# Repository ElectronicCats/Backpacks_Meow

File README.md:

# Backpacks Meow Meow

> WARNING: The Backpacks for Meow Meow are very much still under development and subject to change. If you would like to contribute features and ideas, please send pullrequest to this github repository or file an issue.

## Backpacks

### JACDAC

The JACDAC Connect system uses the JACDAC (Joint Asynchronous Communications) protocol, a single cable transmission protocol for the plug and play of accessories for microcontrollers.

We have adapted this technology to unlock the following benefits:

- No welding between JACDAC breakouts
- Connectors with 3.5mm audio plug to avoid connection errors.
- Ability to create a chain in series where you can connect multiple devices.

More [info about JACDAC](https://jacdac.org/)

### BLE HID
Add wireless connection functionality to your Meow Meow thanks to bluetooth 4.0

## LICENSE

Hardware released under an CERN Open Hardware Licence v1.2. See the LICENSE_HARDWARE file for more information.

Designed by Electronic Cats.

Electronic Cats is a registered trademark, please do not use if you sell these PCBs.

Electronic Cats invests time and resources providing this open source design, please support Electronic Cats and open-source hardware by purchasing products from Electronic Cats!

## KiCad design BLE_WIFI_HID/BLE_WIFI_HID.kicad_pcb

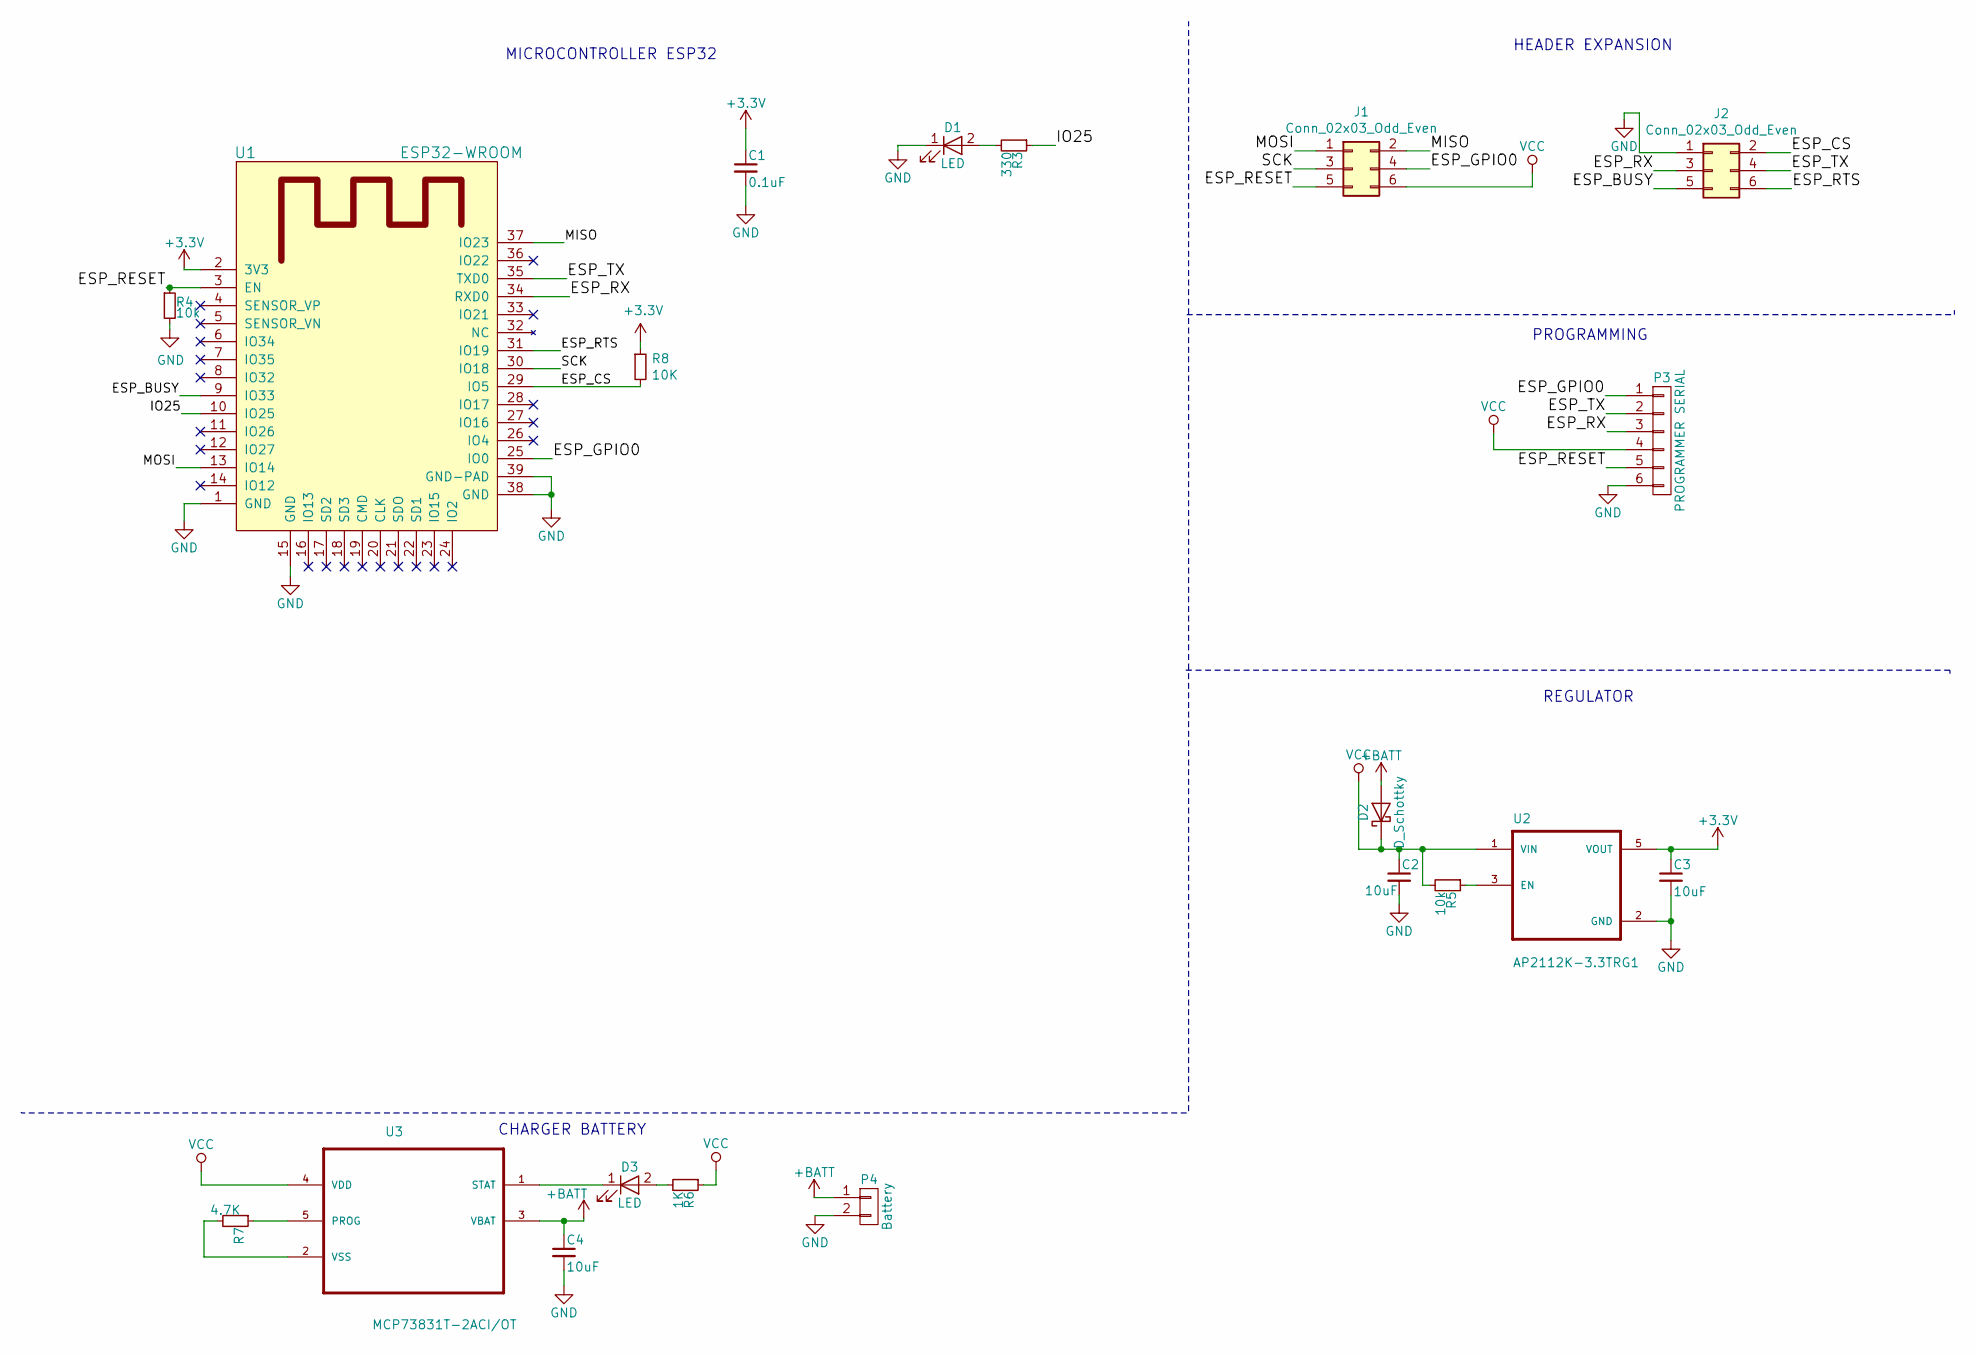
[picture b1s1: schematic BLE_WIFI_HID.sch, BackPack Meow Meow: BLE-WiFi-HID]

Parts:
C1: 0.1uF; C_0805_HandSoldering
C2, C3, C4: 10uF; C_0805_HandSoldering
D1, D3: LED; LED_0805_HandSoldering
D2: D_Schottky; D_SOD-123F
J1, J2: Conn_02x03_Odd_Even; 62000621121
P3: PROGRAMMER SERIAL; Pin_Header_Straight_1x06_Pitch2.54mm
P4: Battery; Pin_Header_Straight_1x02_Pitch2.54mm
R3: 330; R_0805_HandSoldering
R4, R5: 10k; R_0805_HandSoldering
R6: 1K; R_0805_HandSoldering
R7: 4.7K; R_0805_HandSoldering
R8: 10K; R_0805_HandSoldering
U1: ESP32-WROOM
U2: AP2112K-3.3TRG1; SOT-23-5_HandSoldering
U3: MCP73831T-2ACI/OT; SOT-23-5_HandSoldering

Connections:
+3V3: C1.1, C3.1, R8.1, U1.2 (3V3), U2.5 (VOUT)
+BATT: C4.1, D2.2 (A), P4.1, U3.3 (VBAT); also elsewhere on the board
/ESP_BUSY: J2.5, U1.9 (IO33)
/ESP_CS: J2.2, R8.2, U1.29 (IO5)
/ESP_GPIO0: J1.4, P3.1, U1.25 (IO0)
/ESP_RESET: J1.5, P3.5, R4.1, U1.3 (EN)
/ESP_RTS: J2.6, U1.31 (IO19)
/ESP_RX: J2.3, P3.3, U1.34 (RXD0)
/ESP_TX: J2.4, P3.2, U1.35 (TXD0)
/IO25: R3.1, U1.10 (IO25)
/MISO: J1.2, U1.37 (IO23)
/MOSI: J1.1, U1.13 (IO14)
/SCK: J1.3, U1.30 (IO18)
GND: C1.2, C2.2, C3.2, C4.2, D1.1 (K), J2.1, P3.6, P4.2, R4.2, U1.1 (GND), U1.15 (GND), U1.38 (GND), U1.39 (GND-PAD), U2.2 (GND); also elsewhere on the board
unnamed: D1.2 (A), R3.2
unnamed: D3.1 (K), U3.1 (STAT)
unnamed: D3.2 (A), R6.2
unnamed: R5.1, U2.3 (EN)
unnamed: R7.1, U3.5 (PROG)
unnamed: R7.2, U3.2 (VSS)
VCC: C2.1, D2.1 (K), J1.6, P3.4, R5.2, R6.1, U2.1 (VIN), U3.4 (VDD)

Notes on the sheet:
MICROCONTROLLER ESP32
HEADER EXPANSION
PROGRAMMING
CHARGER BATTERY
REGULATOR

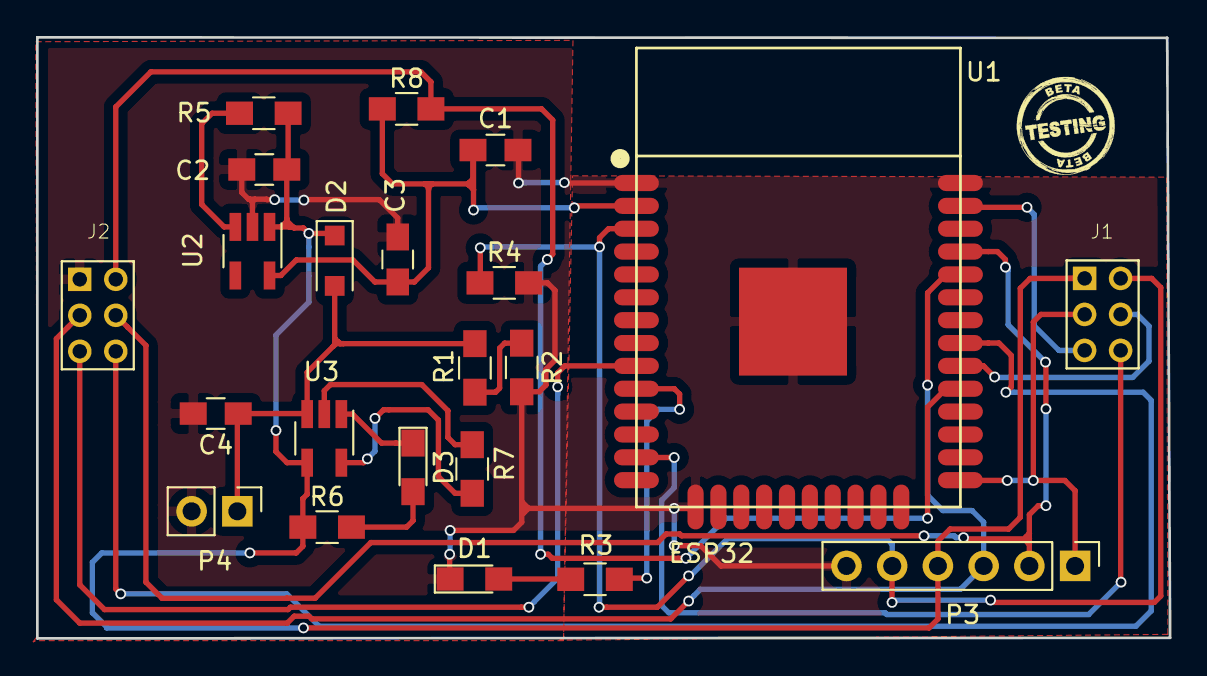
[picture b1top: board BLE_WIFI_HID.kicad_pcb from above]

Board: 2 copper layers, 62.9 x 33.4 mm, 22 parts (0 on the bottom side), 22 nets.

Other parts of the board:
R1, R2: 100k; R_0805_HandSoldering

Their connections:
+BATT: R1.1; also elsewhere on the board
/AN35_BAT: R1.2, R2.1
GND: R2.2; also elsewhere on the board

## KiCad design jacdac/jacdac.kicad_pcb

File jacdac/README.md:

# Make JACDAC System with Meow Meow Backpack

> **Status Tutorial: Experimental**

This tutorial shows you how to build your own MakeCode JACDAC using an [Meow Meow](https://www.electroniccats.com) as the controller sensors device.

## Parts needed

Before you begin, you're going to need a few parts which are shown in the diagram below.

Also, here's a list of where you can buy the parts and a brief description of what each part does too.

* 2 x [Meow Meow](https://www.electroniccats.com) - This will run the code for the project you will be creating.
* 2 x [Meow Meow Backpack JACDAC](https://) - This will connect the Meow Meow to other Meow Meow, using our JACDAC protocol. 

# ALERT:

> **Always** only one device Meow Meow at a time must be connected to the computer.
> 
> Before starting, you must disconnect all the Meow Meows from the USB cable or any other external power supply

## Assembling your MakeCode

The diagram shown at the beginning is what we're going to build as we connect everything together.

### Step 1: Open Maker MakeCode
Open your browser and go to [https://maker.makecode.com/](https://maker.makecode.com/), open "New Project" and select the board Meow Meow, select in mode Javascript your editor code.

### Step 2: Connecting the 3.5mm Audio Jack Connector to the "Meow Meow Host" to the others "Meow Meow Peripheral"

Using a standard audio cable, connect your Meow Meow Host to the Meow Meows Peripheral, as shown in the picture below.

**[!Need an Meow Meow board connection image to go here!](#)**

It does not matter in which connector you place the cable and it is not necessary to make any other connection.

### Step 3: Load an example that uses JACDAC onto the Meow Meow Host 

As mentioned earlier, we're going to be using the protocol called JACDAC to connect the Meow Meow with others Meow Meow to a controller.

Load this code from MakeCode onto your Meow Meow Host:

```typescript-ignore
jacdac.keyboardService.start()
```
 
For more information on the JACDAC protocol, check out this link: [https://jacdac.org/](https://jacdac.org/
)

### Step 4: Load controller code onto Meow Meow Peripheral that uses JACDAC

The Meow Meows Peripheral serves as our controllers for the Meow Meow Host. 

Load this code from MakeCode (beta) onto your Meow Meows Peripherals to use it as a keyboard:

```typescript-ignore
enum JacDacMessage {
    message1 = 49434,
    start = 56380
}
input.touchA0.onEvent(ButtonEvent.Down, function () {
    jacdac.keyboardClient.mediaKey(JDKeyboardMediaKey.Mute, JDKeyboardKeyEvent.Press)
})
input.touchA5.onEvent(ButtonEvent.Down, function () {
    jacdac.keyboardClient.key("a", JDKeyboardKeyEvent.Press)
})
input.touchA1.onEvent(ButtonEvent.Down, function () {
    jacdac.keyboardClient.mediaKey(JDKeyboardMediaKey.VolumeUp, JDKeyboardKeyEvent.Press)
})
input.touchA2.onEvent(ButtonEvent.Down, function () {
    jacdac.keyboardClient.mediaKey(JDKeyboardMediaKey.VolumeDown, JDKeyboardKeyEvent.Press)
})
input.touchA3.onEvent(ButtonEvent.Down, function () {
    jacdac.keyboardClient.key("b", JDKeyboardKeyEvent.Press)
})
input.touchA4.onEvent(ButtonEvent.Down, function () {
    jacdac.keyboardClient.key("b", JDKeyboardKeyEvent.Press)
})
```

### Step 5: Connect the Meow Meow Host to PC

> Remember **always** only one device Meow Meow at a time must be connected to the computer.

After everything is plugged in, turn on the Meow Meow Host and start playing!!

Enjoy!

## TODO

* Add pictures
* Add gifs of example game running

## Resources

### Developer

* [Makecode Maker (beta)](https://maker.makecode.com/beta)
* [JACDAC](https://jacdac.org/)
* [ElectronicCats](https://www.electroniccats.com)

### Components

* [Meow Meow](https://www.electroniccats.com)
* [Meow Meow Backpack JACDAC](https://www.adafruit.com/product/2791/)

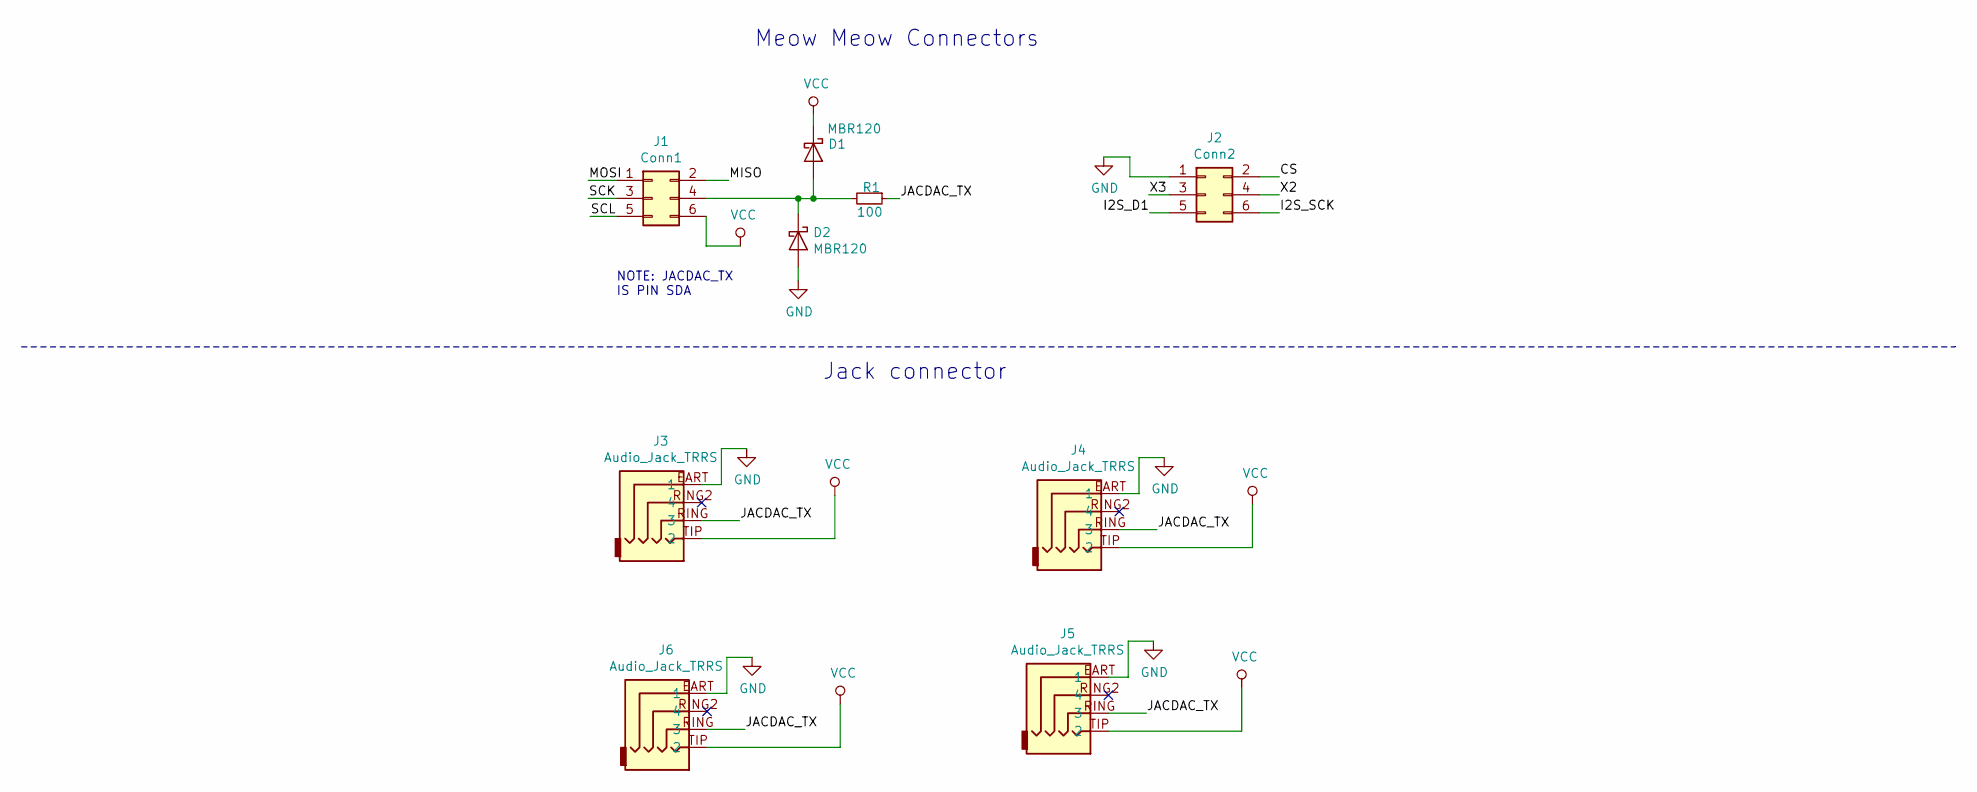
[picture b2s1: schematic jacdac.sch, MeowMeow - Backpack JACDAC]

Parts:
D1, D2: MBR120; D_SOD-123F
J1: Conn1; 61300621121
J2: Conn2; 61300621121
J3, J4, J5, J6: Audio_Jack_TRRS; AUDIO-JACK-TRRS-SMD
R1: 100; R_0805_HandSoldering

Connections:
/CS: J2.2
/I2S_D1: J2.5
/I2S_SCK: J2.6
/JACDAC_TX: J3.RING (3), J4.RING (3), J5.RING (3), J6.RING (3), R1.1
/MISO: J1.2
/MOSI: J1.1
/SCK: J1.3
/SCL: J1.5
/X2: J2.4
/X3: J2.3
GND: D2.2 (A), J2.1, J3.EART (1), J4.EART (1), J5.EART (1), J6.EART (1)
unnamed: D1.2 (A), D2.1 (K), J1.4, R1.2
VCC: D1.1 (K), J1.6, J3.TIP (2), J4.TIP (2), J5.TIP (2), J6.TIP (2)

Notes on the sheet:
Meow Meow Connectors
NOTE: JACDAC_TX IS PIN SDA
Jack connector

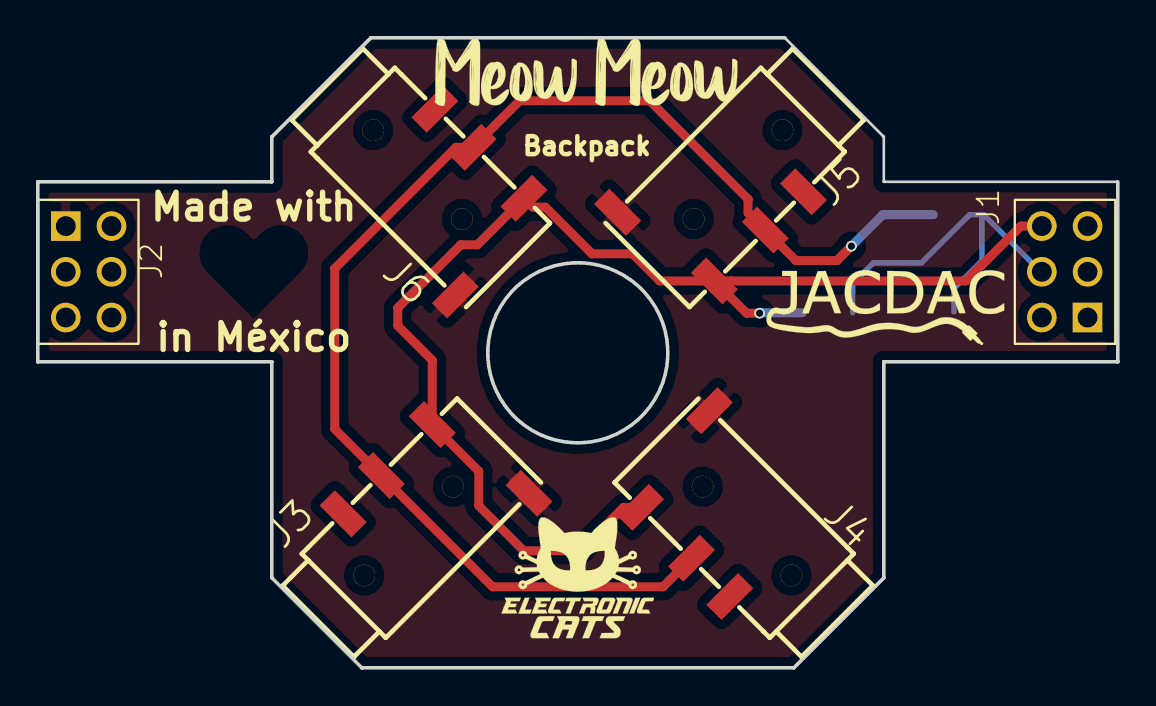
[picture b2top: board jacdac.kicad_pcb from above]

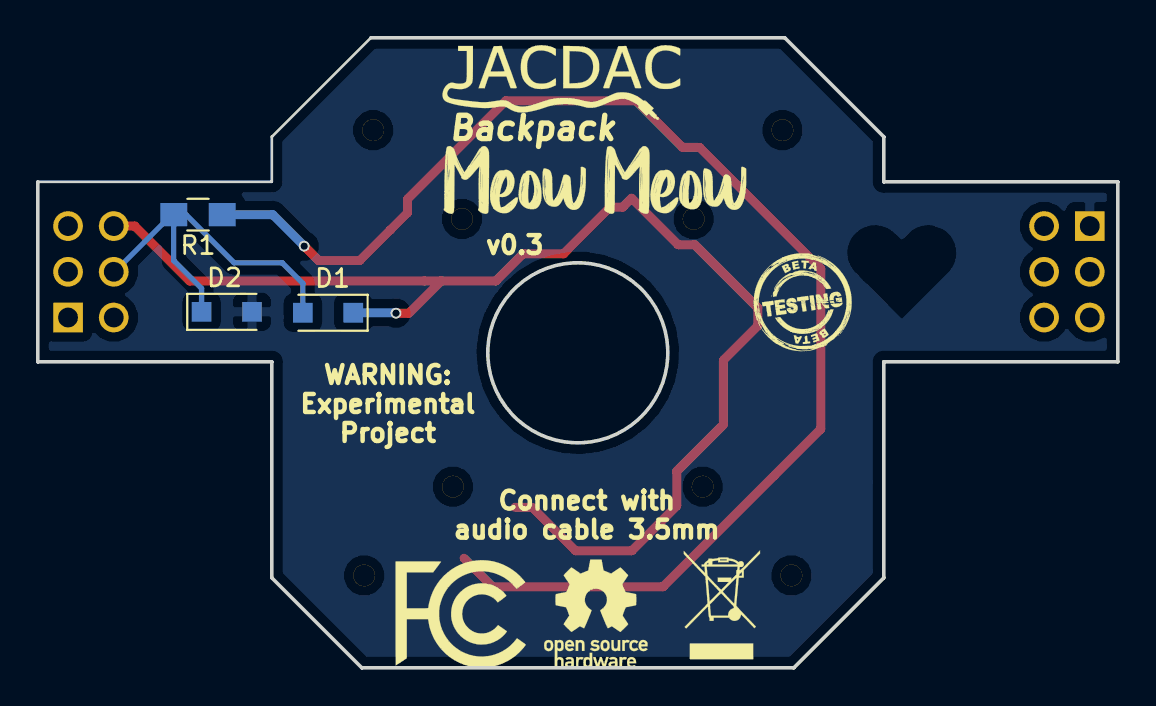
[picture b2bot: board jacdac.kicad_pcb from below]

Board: 2 copper layers, 60.0 x 35.0 mm, 11 parts (4 on the bottom side), 4 nets.

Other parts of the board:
svg2mod, svg2mod#2: G***; heart_trans

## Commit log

2018-06-26 V0.1
2018-06-28 Miss one pin and clear
2018-06-29 clean and new position
2018-06-29 change the connectors
2018-06-29 Firmware init for platformio
2018-07-02 Auto stash before merge of "master" and "origin/master"
2018-07-08 Rename and update example
2019-02-11 init backpack jacdac
2019-02-11 one connector 4 pines
2019-02-13 update schematic to audio TRRS
2019-02-13 init PCB
2019-02-13 add gitignore
2019-02-14 update PCB
2019-02-14 add logo jacdac
2019-02-14 fix pin number jack TRRS
2019-02-19 new headers
2019-02-19 mode star
2019-02-19 version for test
2019-02-19 update README for JACDAC
2019-02-21 Label experimental project
    experimental project!!!
2019-02-21 version beta testing
2019-02-25 add schematic pdf
2019-02-25 init v0.2 add diodes and resistor
2019-02-26 Init Make JACDAC System
2019-03-04 Init README
2019-03-04 add makecode
2019-03-05 Fix GND inverted
2019-03-17 WIFININA new
2019-03-17 change headers expansion
2019-03-18 update to v0.3 pcb
2019-03-27 bump :D
2019-03-27 update reset resistor ESP32
2019-07-11 Inicio routeo
2019-07-12 Acomodo conectores
2019-07-15 batt and reset
2019-07-15 Change Esp
2019-07-15 Ground plane
2019-07-17 Conn left
2019-07-17 Conn rigth
2019-08-03 re-routeo
2019-08-13 Component number
2019-08-14 Version beta BLE and WIFI NINA
